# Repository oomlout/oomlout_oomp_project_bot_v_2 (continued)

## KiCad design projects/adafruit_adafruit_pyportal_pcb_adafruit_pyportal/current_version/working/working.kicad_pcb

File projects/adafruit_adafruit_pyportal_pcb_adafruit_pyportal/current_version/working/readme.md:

# adafruit_pyportal_pcb
 
## summary 
* id: adafruit_adafruit_pyportal_pcb_adafruit_pyportal
* user: adafruit
* name: adafruit_pyportal_pcb
* board: adafruit_pyportal
* repo: https://github.com/adafruit/Adafruit-PyPortal-PCB

* src_file_repo_sch: 
* src_file_repo_sch_link: https://github.com/adafruit/Adafruit-PyPortal-PCB/tree/master/
* full details link: https://github.com/oomlout/oomlout_oomp_project_bot_v_2/tree/main/projects/adafruit_adafruit_pyportal_pcb_adafruit_pyportal/current_version/working  

## schematic  
  
[schematic (pdf)](working_schematic.pdf) 

## pcb  

[board (pdf)](working.pdf)  

## working_bom
| Id | Designator | Footprint | Quantity | Designation | Supplier and ref |  | None | 
| --- | --- | --- | --- | --- | --- | --- | --- | 
| 1 | C17,C19,C1 | 0603-NO | 3 | 0.1uF |  |  | [''] | 
| 2 | R20,R19,R15,R18,R6,R9,R8 | 0603-NO | 7 | 10K |  |  | [''] | 
| 3 | U$2 | PQFN64-1 | 1 | ATSAMD51J20 |  |  | [''] | 
| 4 | D2,D1 | SOD-323 | 2 | 3.6V |  |  | [''] | 
| 5 | X3 | 2X05_1.27MM_SMT | 1 | 2x5 0.05 SWD" |  |  | [''] | 
| 6 | C14,C16,C11,C15,C12,C10 | 0603-NO | 6 | .1u |  |  | [''] | 
| 7 | CON1 | 53398-0271 | 1 | CON_MOLEX_2P |  |  | [''] | 
| 8 | LED1 | LED3535 | 1 | WS2812B3535 |  |  | [''] | 
| 9 | U$16,U$7,U$15,U$17 | MOUNTINGHOLE_3.0_PLATEDTHIN | 4 | MOUNTINGHOLE3.0THIN |  |  | [''] | 
| 10 | TP8,TP9,TP7 | TESTPOINT_ROUND_1.5MM | 3 |  |  |  | [''] | 
| 11 | U$23,U$11,U$9 | FIDUCIAL_1MM | 3 | FIDUCIAL_1MM |  |  | [''] | 
| 12 | C24,C3,C13,C22,C2,C20,C23,C5,C18,C8,C7,C21,C6 | 0805-NO | 13 | 10uF |  |  | [''] | 
| 13 | IC2 | SOT23-6 | 1 | PAM8301 |  |  | [''] | 
| 14 | R21,R22 | 0603-NO | 2 | 47K |  |  | [''] | 
| 15 | SJ4 | SOLDERJUMPER_CLOSEDWIRE | 1 |  |  |  | [''] | 
| 16 | X1 | MICROSD | 1 | microSD |  |  | [''] | 
| 17 | X4 | 4UCONN_20329_NARROW | 1 | microUSB |  |  | [''] | 
| 18 | R5,R12,R11,R10 | 0603-NO | 4 | 1K |  |  | [''] | 
| 19 | U4 | ALS-PT26-21C | 1 | ALS-PT21 |  |  | [''] | 
| 20 | RESET0 | EVQ-Q2_SMALLER | 1 | EVQQ 6mm |  |  | [''] | 
| 21 | R13 | RESPACK_4X0603 | 1 | 100 |  |  | [''] | 
| 22 | U1 | SOT23-5 | 1 | AP2112-3.3 |  |  | [''] | 
| 23 | Q1 | SOT23-BEC | 1 | MMBT2222 |  |  | [''] | 
| 24 | I2C0 | JSTPH4 | 1 | JST PH 4 |  |  | [''] | 
| 25 | SP1 | BUZZER_SMT_7.5MM | 1 | 7.5mm SPK |  |  | [''] | 
| 26 | PTC1 | 1206 | 1 | 500mA |  |  | [''] | 
| 27 | NEOPIX0,SENSE0 | JSTPH3 | 2 | JST PH 3 |  |  | [''] | 
| 28 | IC1 | SOT23-5L | 1 | 74AHC1G125 |  |  | [''] | 
| 29 | R4 | RESPACK_4X0603 | 1 | 10K |  |  | [''] | 
| 30 | C4 | 0805-NO | 1 | 0.1uF |  |  | [''] | 
| 31 | U$19 | PYPORTALPYNT_TOP | 1 |  |  |  | [''] | 
| 32 | U2 | SOIC8_208MIL | 1 | GD25Q64 |  |  | [''] | 
| 33 | IC3 | SOIC8_150MIL | 1 | ATECCX08 |  |  | [''] | 
| 34 | Q4 | SOT363 | 1 | BSS138 |  |  | [''] | 
| 35 | U$63 | PCBFEAT-REV-040 | 1 |  |  |  | [''] | 
| 36 | L0 | CHIPLED_0805_NOOUTLINE | 1 | RED |  |  | [''] | 
| 37 | U3 | ARDUINO-UCS&SOCS_NINA-W1X | 1 | NINA-W102 |  |  | [''] | 
| 38 | SJ1 | SOLDERJUMPER_2WAY_OPEN_NOPASTE | 1 |  |  |  | [''] | 
| 39 | C9 | 0603-NO | 1 | 1uF |  |  | [''] | 
| 40 | U$55 | TFT_2.4IN_240X320_50PIN | 1 | DISP_LCD_240X320_50PIN-2.4IN |  |  | [''] | 
| 41 | U$54 | PYPORTALPYNT_BOT | 1 |  |  |  | [''] | 

## bom_schematic
| Ref | Qnty | Value | Cmp name | Footprint | Description | Vendor | DNP | 
| --- | --- | --- | --- | --- | --- | --- | --- | 
| C1, C17, C19 | 3 | 0.1uF | CAP_CERAMIC0603_NO | working:0603-NO |  |  |  | 
| C2, C3, C5, C6, C7, C8, C13, C18, C20, C21, C22, C23, C24 | 13 | 10uF | CAP_CERAMIC0805-NOOUTLINE | working:0805-NO |  |  |  | 
| C4 | 1 | 0.1uF | CAP_CERAMIC0805-NOOUTLINE | working:0805-NO |  |  |  | 
| C9 | 1 | 1uF | CAP_CERAMIC0603_NO | working:0603-NO |  |  |  | 
| C10, C11, C12, C14, C15, C16 | 6 | .1u | CAP_CERAMIC0603_NO | working:0603-NO |  |  |  | 
| CON1 | 1 | CON_MOLEX_2P | CON_MOLEX_2P | working:53398-0271 |  |  |  | 
| D1, D2 | 2 | 3.6V | DIODE-ZENERSOD323 | working:SOD-323 |  |  |  | 
| I2C0 | 1 | STEMMA_I2C_RASMT | STEMMA_I2C_RASMT | working:JSTPH4 |  |  |  | 
| IC1 | 1 | 74AHC1G125 | 74AHC1G125 | working:SOT23-5L |  |  |  | 
| IC2 | 1 | PAM8301 | PAM8301 | working:SOT23-6 |  |  |  | 
| IC3 | 1 | ATECCX08 | ATECCX08 | working:SOIC8_150MIL |  |  |  | 
| L0 | 1 | RED | LED0805_NOOUTLINE | working:CHIPLED_0805_NOOUTLINE |  |  |  | 
| LED1 | 1 | WS2812B3535 | WS2812B3535 | working:LED3535 |  |  |  | 
| NEOPIX0 | 1 | JST PH 3 | CON_JST_PH_3PIN | working:JSTPH3 |  |  |  | 
| PTC1 | 1 | 500mA | PTC1206 | working:1206 |  |  |  | 
| Q1 | 1 | MMBT2222 | -NPN-SOT23-BEC | working:SOT23-BEC |  |  |  | 
| Q4 | 1 | BSS138 | MOSFET-N_DUAL | working:SOT363 |  |  |  | 
| R4 | 1 | 10K | RESISTOR_4PACK | working:RESPACK_4X0603 |  |  |  | 
| R5, R10, R11, R12 | 4 | 1K | RESISTOR_0603_NOOUT | working:0603-NO |  |  |  | 
| R6, R8, R9, R15, R18, R19, R20 | 7 | 10K | RESISTOR_0603_NOOUT | working:0603-NO |  |  |  | 
| R13 | 1 | 100 | RESISTOR_4PACK | working:RESPACK_4X0603 |  |  |  | 
| R21, R22 | 2 | 47K | RESISTOR_0603_NOOUT | working:0603-NO |  |  |  | 
| RESET0 | 1 | EVQQ 6mm | SWITCH_TACT_SMT_EVQQ2_SMALL | working:EVQ-Q2_SMALLER |  |  |  | 
| SENSE0 | 1 | JST PH 3 | CON_JST_PH_3PIN | working:JSTPH3 |  |  |  | 
| SJ1 | 1 | SOLDERJUMPER_2WAY | SOLDERJUMPER_2WAY | working:SOLDERJUMPER_2WAY_OPEN_NOPASTE |  |  |  | 
| SJ4 | 1 | SOLDERJUMPERCLOSED | SOLDERJUMPERCLOSED | working:SOLDERJUMPER_CLOSEDWIRE |  |  |  | 
| SP1 | 1 | SPEAKER_7.5MM | SPEAKER_7.5MM | working:BUZZER_SMT_7.5MM |  |  |  | 
| TP7, TP8, TP9 | 3 | TESTPOINTROUND1.5MM | TESTPOINTROUND1.5MM | working:TESTPOINT_ROUND_1.5MM |  |  |  | 
| U1 | 1 | AP2112-3.3 | VREG_SOT23-5 | working:SOT23-5 |  |  |  | 
| U2 | 1 | GD25Q64 | SPIFLASH_8PIN208MIL | working:SOIC8_208MIL |  |  |  | 
| U3 | 1 | NINA-W10XNINA-W10X | NINA-W10XNINA-W10X | working:ARDUINO-UCS&SOCS_NINA-W1X |  |  |  | 
| U4 | 1 | ALS-PT21 | PHOTOTRANSISTOR_PT26-21C | working:ALS-PT26-21C |  |  |  | 
| U$2 | 1 | ATSAMD51J | ATSAMD51J | working:PQFN64-1 |  |  |  | 
| U$7, U$15, U$16, U$17 | 4 | MOUNTINGHOLE3.0THIN | MOUNTINGHOLE3.0THIN | working:MOUNTINGHOLE_3.0_PLATEDTHIN |  |  |  | 
| U$9, U$11, U$23 | 3 | FIDUCIAL_1MM | FIDUCIAL_1MM | working:FIDUCIAL_1MM |  |  |  | 
| U$55 | 1 | DISP_LCD_240X320_50PIN-2.4IN | DISP_LCD_240X320_50PIN-2.4IN | working:TFT_2.4IN_240X320_50PIN |  |  |  | 
| X1 | 1 | microSD | MICROSD | working:MICROSD |  |  |  | 
| X3 | 1 | 2x5 0.05" SWD | JTAG-CORTEX | working:2X05_1.27MM_SMT |  |  |  | 
| X4 | 1 | microUSB | USB_MICRO_NARROW | working:4UCONN_20329_NARROW |  |  |  | 

## mounting_holes
| x | y | package | value | ref | size | 
| --- | --- | --- | --- | --- | --- | 
| 61.72 | 0.0 | MOUNTINGHOLE_3.0_PLATEDTHIN | MOUNTINGHOLE3.0THIN | U$7 | m3 | 
| 61.72 | 47.88 | MOUNTINGHOLE_3.0_PLATEDTHIN | MOUNTINGHOLE3.0THIN | U$15 | m3 | 
| 0.0 | 0.0 | MOUNTINGHOLE_3.0_PLATEDTHIN | MOUNTINGHOLE3.0THIN | U$16 | m3 | 
| 0.0 | 47.88 | MOUNTINGHOLE_3.0_PLATEDTHIN | MOUNTINGHOLE3.0THIN | U$17 | m3 |

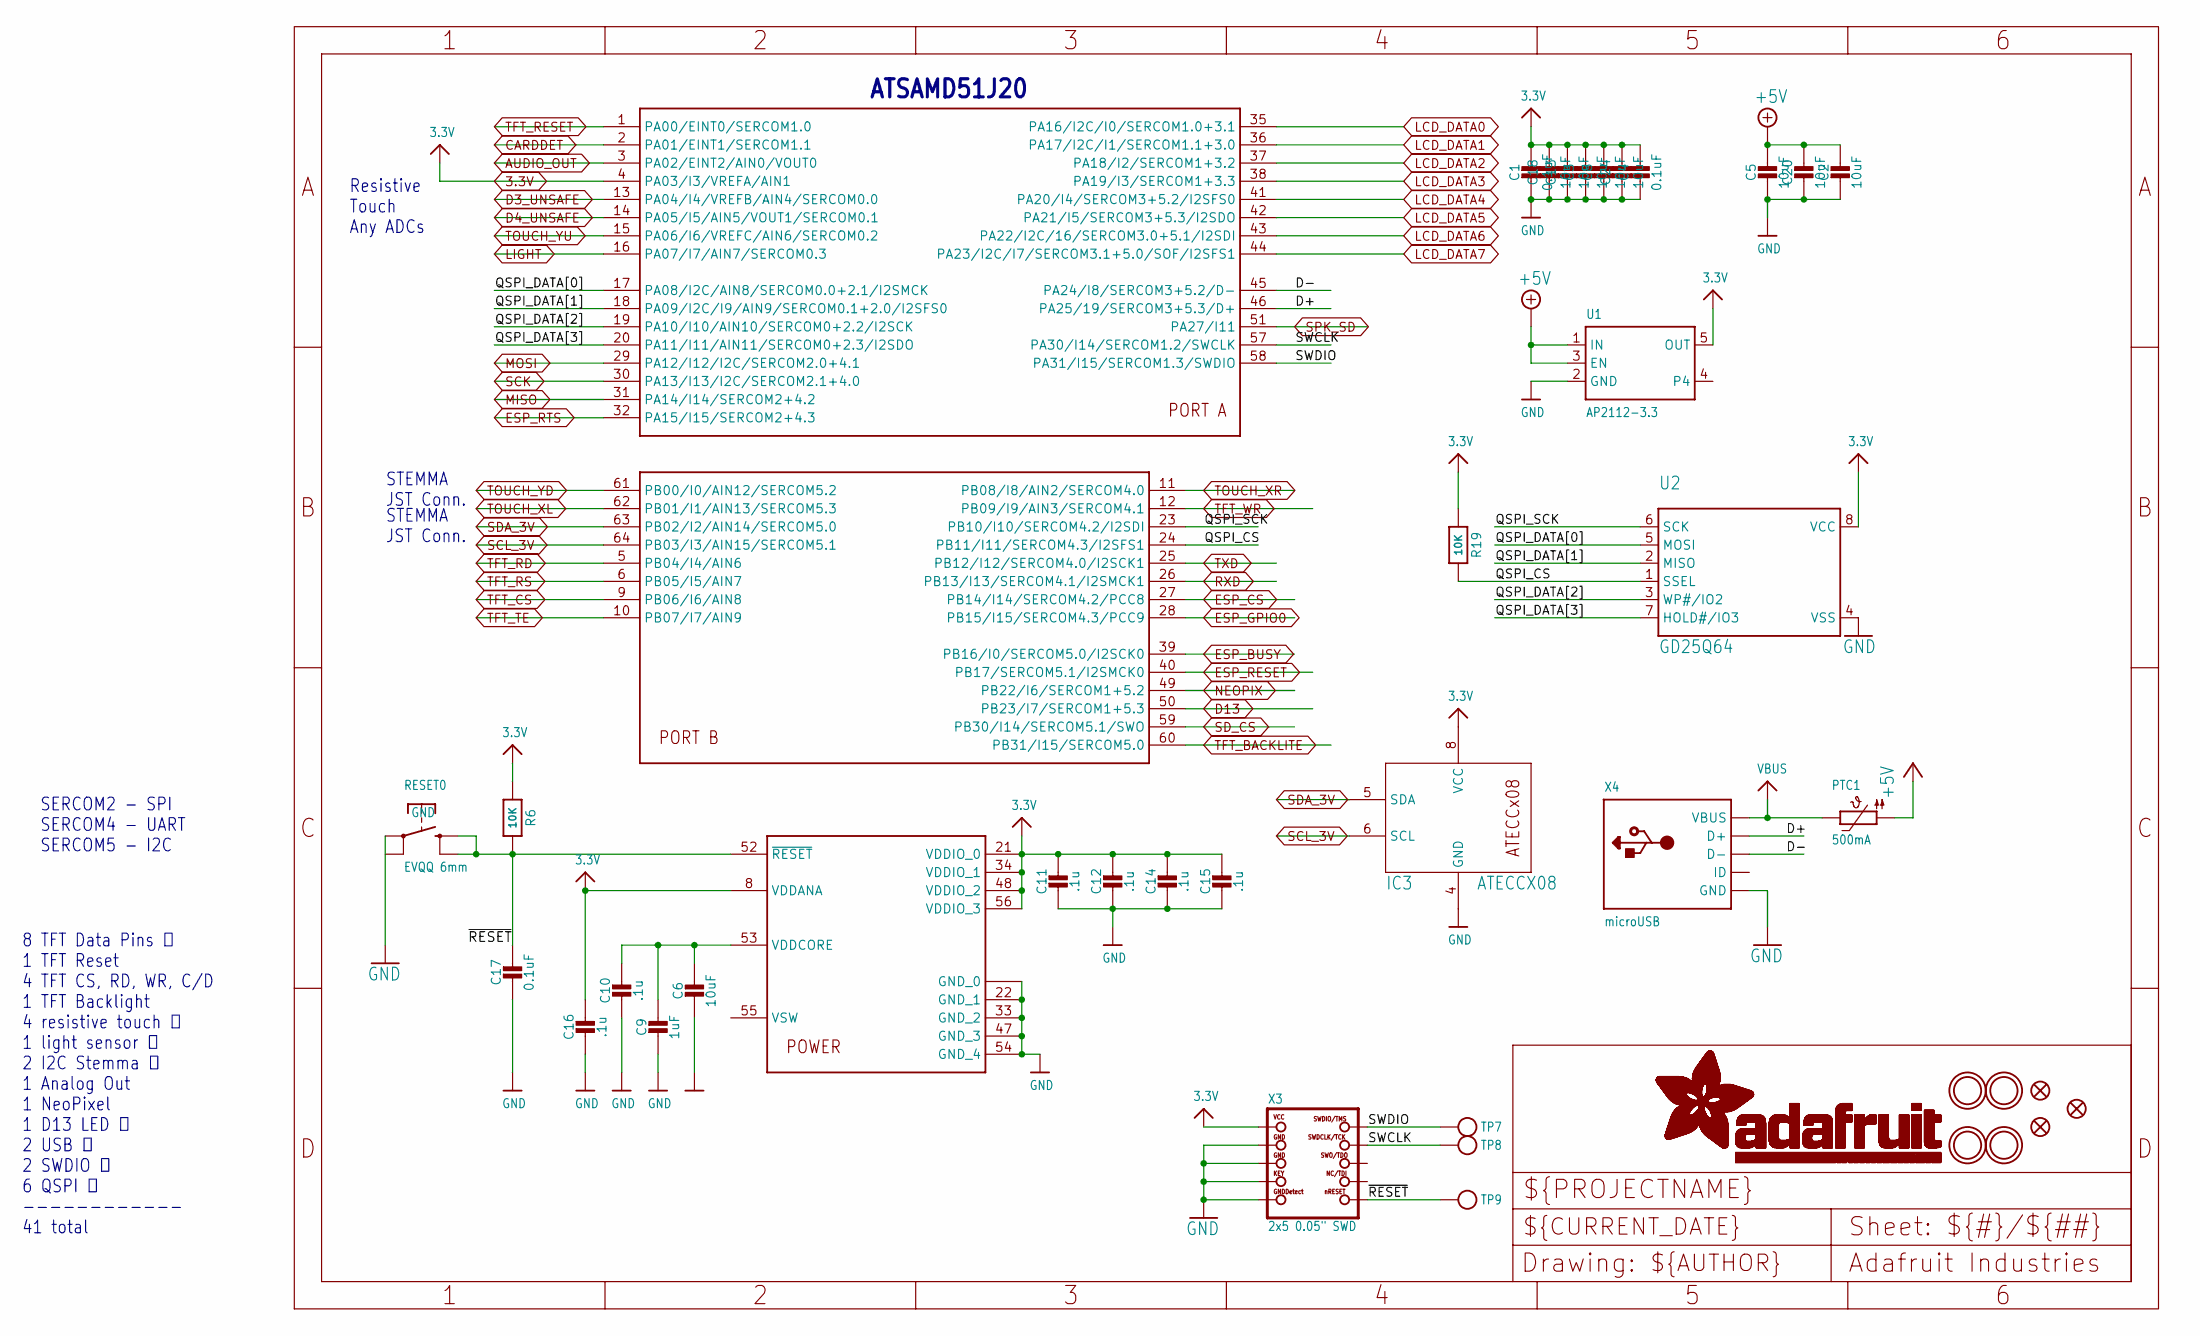
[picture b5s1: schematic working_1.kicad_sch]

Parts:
C1, C17: 0.1uF; 0603-NO
C2, C3, C5, C6, C8, C13, C18, C20, C24: 10uF; 0805-NO
C4: 0.1uF; 0805-NO
C9: 1uF; 0603-NO
C10, C11, C12, C14, C15, C16: .1u; 0603-NO
IC3: ATECCX08; SOIC8_150MIL
PTC1: 500mA; 1206
R6, R19: 10K; 0603-NO
RESET0: EVQQ 6mm; EVQ-Q2_SMALLER
TP7, TP8, TP9: TESTPOINTROUND1.5MM; TESTPOINT_ROUND_1.5MM
U1: AP2112-3.3; SOT23-5
U2: GD25Q64; SOIC8_208MIL
U$2: ATSAMD51J; PQFN64-1
U$7, U$15, U$16, U$17: MOUNTINGHOLE3.0THIN; MOUNTINGHOLE_3.0_PLATEDTHIN
U$9, U$11, U$23: FIDUCIAL_1MM
X3: 2x5 0.05" SWD; 2X05_1.27MM_SMT
X4: microUSB; 4UCONN_20329_NARROW

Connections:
3.3V: C1.1, C3.1, C4.1, C8.1, C11.2, C12.2, C13.1, C14.2, C15.2, C16.2, C18.1, C24.1, IC3.8 (VCC), R6.1, R19.1, U1.5 (OUT), U2.8 (VCC), U$2.4 (PA03/I3/VREFA/AIN1), U$2.8 (VDDANA), U$2.21 (VDDIO_0), U$2.34 (VDDIO_1), U$2.48 (VDDIO_2), U$2.56 (VDDIO_3), X3.1 (VCC); also elsewhere on the board
+5V: C2.1, C5.1, C20.1, PTC1.1, U1.1 (IN), U1.3 (EN); also elsewhere on the board
AUDIO_OUT: U$2.3 (PA02/EINT2/AIN0/VOUT0); also elsewhere on the board
CARDDET: U$2.2 (PA01/EINT1/SERCOM1.1); also elsewhere on the board
D3_UNSAFE: U$2.13 (PA04/I4/VREFB/AIN4/SERCOM0.0); also elsewhere on the board
D4_UNSAFE: U$2.14 (PA05/I5/AIN5/VOUT1/SERCOM0.1); also elsewhere on the board
D13: U$2.50 (PB23/I7/SERCOM1+5.3); also elsewhere on the board
D+: U$2.46 (PA25/19/SERCOM3+5.3/D+), X4.D+
D-: U$2.45 (PA24/I8/SERCOM3+5.2/D-), X4.D-
ESP_BUSY: U$2.39 (PB16/I0/SERCOM5.0/I2SCK0); also elsewhere on the board
ESP_CS: U$2.27 (PB14/I14/SERCOM4.2/PCC8); also elsewhere on the board
ESP_GPIO0: U$2.28 (PB15/I15/SERCOM4.3/PCC9); also elsewhere on the board
ESP_RESET: U$2.40 (PB17/SERCOM5.1/I2SMCK0); also elsewhere on the board
ESP_RTS: U$2.32 (PA15/I15/SERCOM2+4.3); also elsewhere on the board
GND: C1.2, C2.2, C3.2, C4.2, C5.2, C6.2, C8.2, C9.2, C10.1, C11.1, C12.1, C13.2, C14.1, C15.1, C16.1, C17.1, C18.2, C20.2, C24.2, IC3.4 (GND), RESET0.A, RESET0.A' (P1), U1.2 (GND), U2.4 (VSS), U$2.7 (GND_0), U$2.22 (GND_1), U$2.33 (GND_2), U$2.47 (GND_3), U$2.54 (GND_4), U$2.EXP (GND_0), X3.3 (GND@1), X3.5 (GND@2), X3.7 (KEY), X3.9 (GNDDETECT), X4.BASE@1 (GND), X4.BASE@2 (GND), X4.GND, X4.SPRT@1 (GND), X4.SPRT@2 (GND), X4.SPRT@3 (GND), X4.SPRT@4 (GND); also elsewhere on the board
LCD_DATA0: U$2.35 (PA16/I2C/I0/SERCOM1.0+3.1); also elsewhere on the board
LCD_DATA1: U$2.36 (PA17/I2C/I1/SERCOM1.1+3.0); also elsewhere on the board
LCD_DATA2: U$2.37 (PA18/I2/SERCOM1+3.2); also elsewhere on the board
LCD_DATA3: U$2.38 (PA19/I3/SERCOM1+3.3); also elsewhere on the board
LCD_DATA4: U$2.41 (PA20/I4/SERCOM3+5.2/I2SFS0); also elsewhere on the board
LCD_DATA5: U$2.42 (PA21/I5/SERCOM3+5.3/I2SDO); also elsewhere on the board
LCD_DATA6: U$2.43 (PA22/I2C/16/SERCOM3.0+5.1/I2SDI); also elsewhere on the board
LCD_DATA7: U$2.44 (PA23/I2C/I7/SERCOM3.1+5.0/SOF/I2SFS1); also elsewhere on the board
LIGHT: U$2.16 (PA07/I7/AIN7/SERCOM0.3); also elsewhere on the board
MISO: U$2.31 (PA14/I14/SERCOM2+4.2); also elsewhere on the board
MOSI: U$2.29 (PA12/I12/I2C/SERCOM2.0+4.1); also elsewhere on the board
NEOPIX: U$2.49 (PB22/I6/SERCOM1+5.2); also elsewhere on the board
QSPI_CS: R19.2, U2.1 (SSEL), U$2.24 (PB11/I11/SERCOM4.3/I2SFS1)
QSPI_DATA[0]: U2.5 (MOSI), U$2.17 (PA08/I2C/AIN8/SERCOM0.0+2.1/I2SMCK)
QSPI_DATA[1]: U2.2 (MISO), U$2.18 (PA09/I2C/I9/AIN9/SERCOM0.1+2.0/I2SFS0)
QSPI_DATA[2]: U2.3 (WP#/IO2), U$2.19 (PA10/I10/AIN10/SERCOM0+2.2/I2SCK)
QSPI_DATA[3]: U2.7 (HOLD#/IO3), U$2.20 (PA11/I11/AIN11/SERCOM0+2.3/I2SDO)
QSPI_SCK: U2.6 (SCK), U$2.23 (PB10/I10/SERCOM4.2/I2SDI)
RXD: U$2.26 (PB13/I13/SERCOM4.1/I2SMCK1); also elsewhere on the board
SCK: U$2.30 (PA13/I13/I2C/SERCOM2.1+4.0); also elsewhere on the board
SCL_3V: IC3.6 (SCL), U$2.64 (PB03/I3/AIN15/SERCOM5.1); also elsewhere on the board
SDA_3V: IC3.5 (SDA), U$2.63 (PB02/I2/AIN14/SERCOM5.0); also elsewhere on the board
SD_CS: U$2.59 (PB30/I14/SERCOM5.1/SWO); also elsewhere on the board
SPK_SD: U$2.51 (PA27/I11); also elsewhere on the board
SWCLK: TP8.P$1, U$2.57 (PA30/I14/SERCOM1.2/SWCLK), X3.4 (SWDCLK)
SWDIO: TP7.P$1, U$2.58 (PA31/I15/SERCOM1.3/SWDIO), X3.2 (SWDIO)
TFT_BACKLITE: U$2.60 (PB31/I15/SERCOM5.0); also elsewhere on the board
TFT_CS: U$2.9 (PB06/I6/AIN8); also elsewhere on the board
TFT_RD: U$2.5 (PB04/I4/AIN6); also elsewhere on the board
TFT_RESET: U$2.1 (PA00/EINT0/SERCOM1.0); also elsewhere on the board
TFT_RS: U$2.6 (PB05/I5/AIN7); also elsewhere on the board
TFT_TE: U$2.10 (PB07/I7/AIN9); also elsewhere on the board
TFT_WR: U$2.12 (PB09/I9/AIN3/SERCOM4.1); also elsewhere on the board
TOUCH_XL: U$2.62 (PB01/I1/AIN13/SERCOM5.3); also elsewhere on the board
TOUCH_XR: U$2.11 (PB08/I8/AIN2/SERCOM4.0); also elsewhere on the board
TOUCH_YD: U$2.61 (PB00/I0/AIN12/SERCOM5.2); also elsewhere on the board
TOUCH_YU: U$2.15 (PA06/I6/VREFC/AIN6/SERCOM0.2); also elsewhere on the board
TXD: U$2.25 (PB12/I12/SERCOM4.0/I2SCK1); also elsewhere on the board
VBUS: PTC1.2, X4.VBUS
VDDCORE: C6.1, C9.1, C10.2, U$2.53 (VDDCORE)
~RESET: C17.2, R6.2, RESET0.B (S), RESET0.B' (S1), TP9.P$1, U$2.52 (~RESET), X3.10 (NRESET)

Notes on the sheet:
Resistive Touch Any ADCs
ATSAMD51J20
STEMMA JST Conn.
SERCOM2 - SPI SERCOM4 - UART SERCOM5 - I2C
8 TFT Data Pins ✓ 1 TFT Reset 4 TFT CS, RD, WR, C/D 1 TFT Backlight 4 resistive touch ✓ 1 light sensor ✓ 2 I2C Stemma ✓ 1 Analog Out 1 NeoPixel 1 D13 LED ✓ 2 USB ✓ 2 SWDIO ✓ 6 QSPI ✓ ------------ 41 total

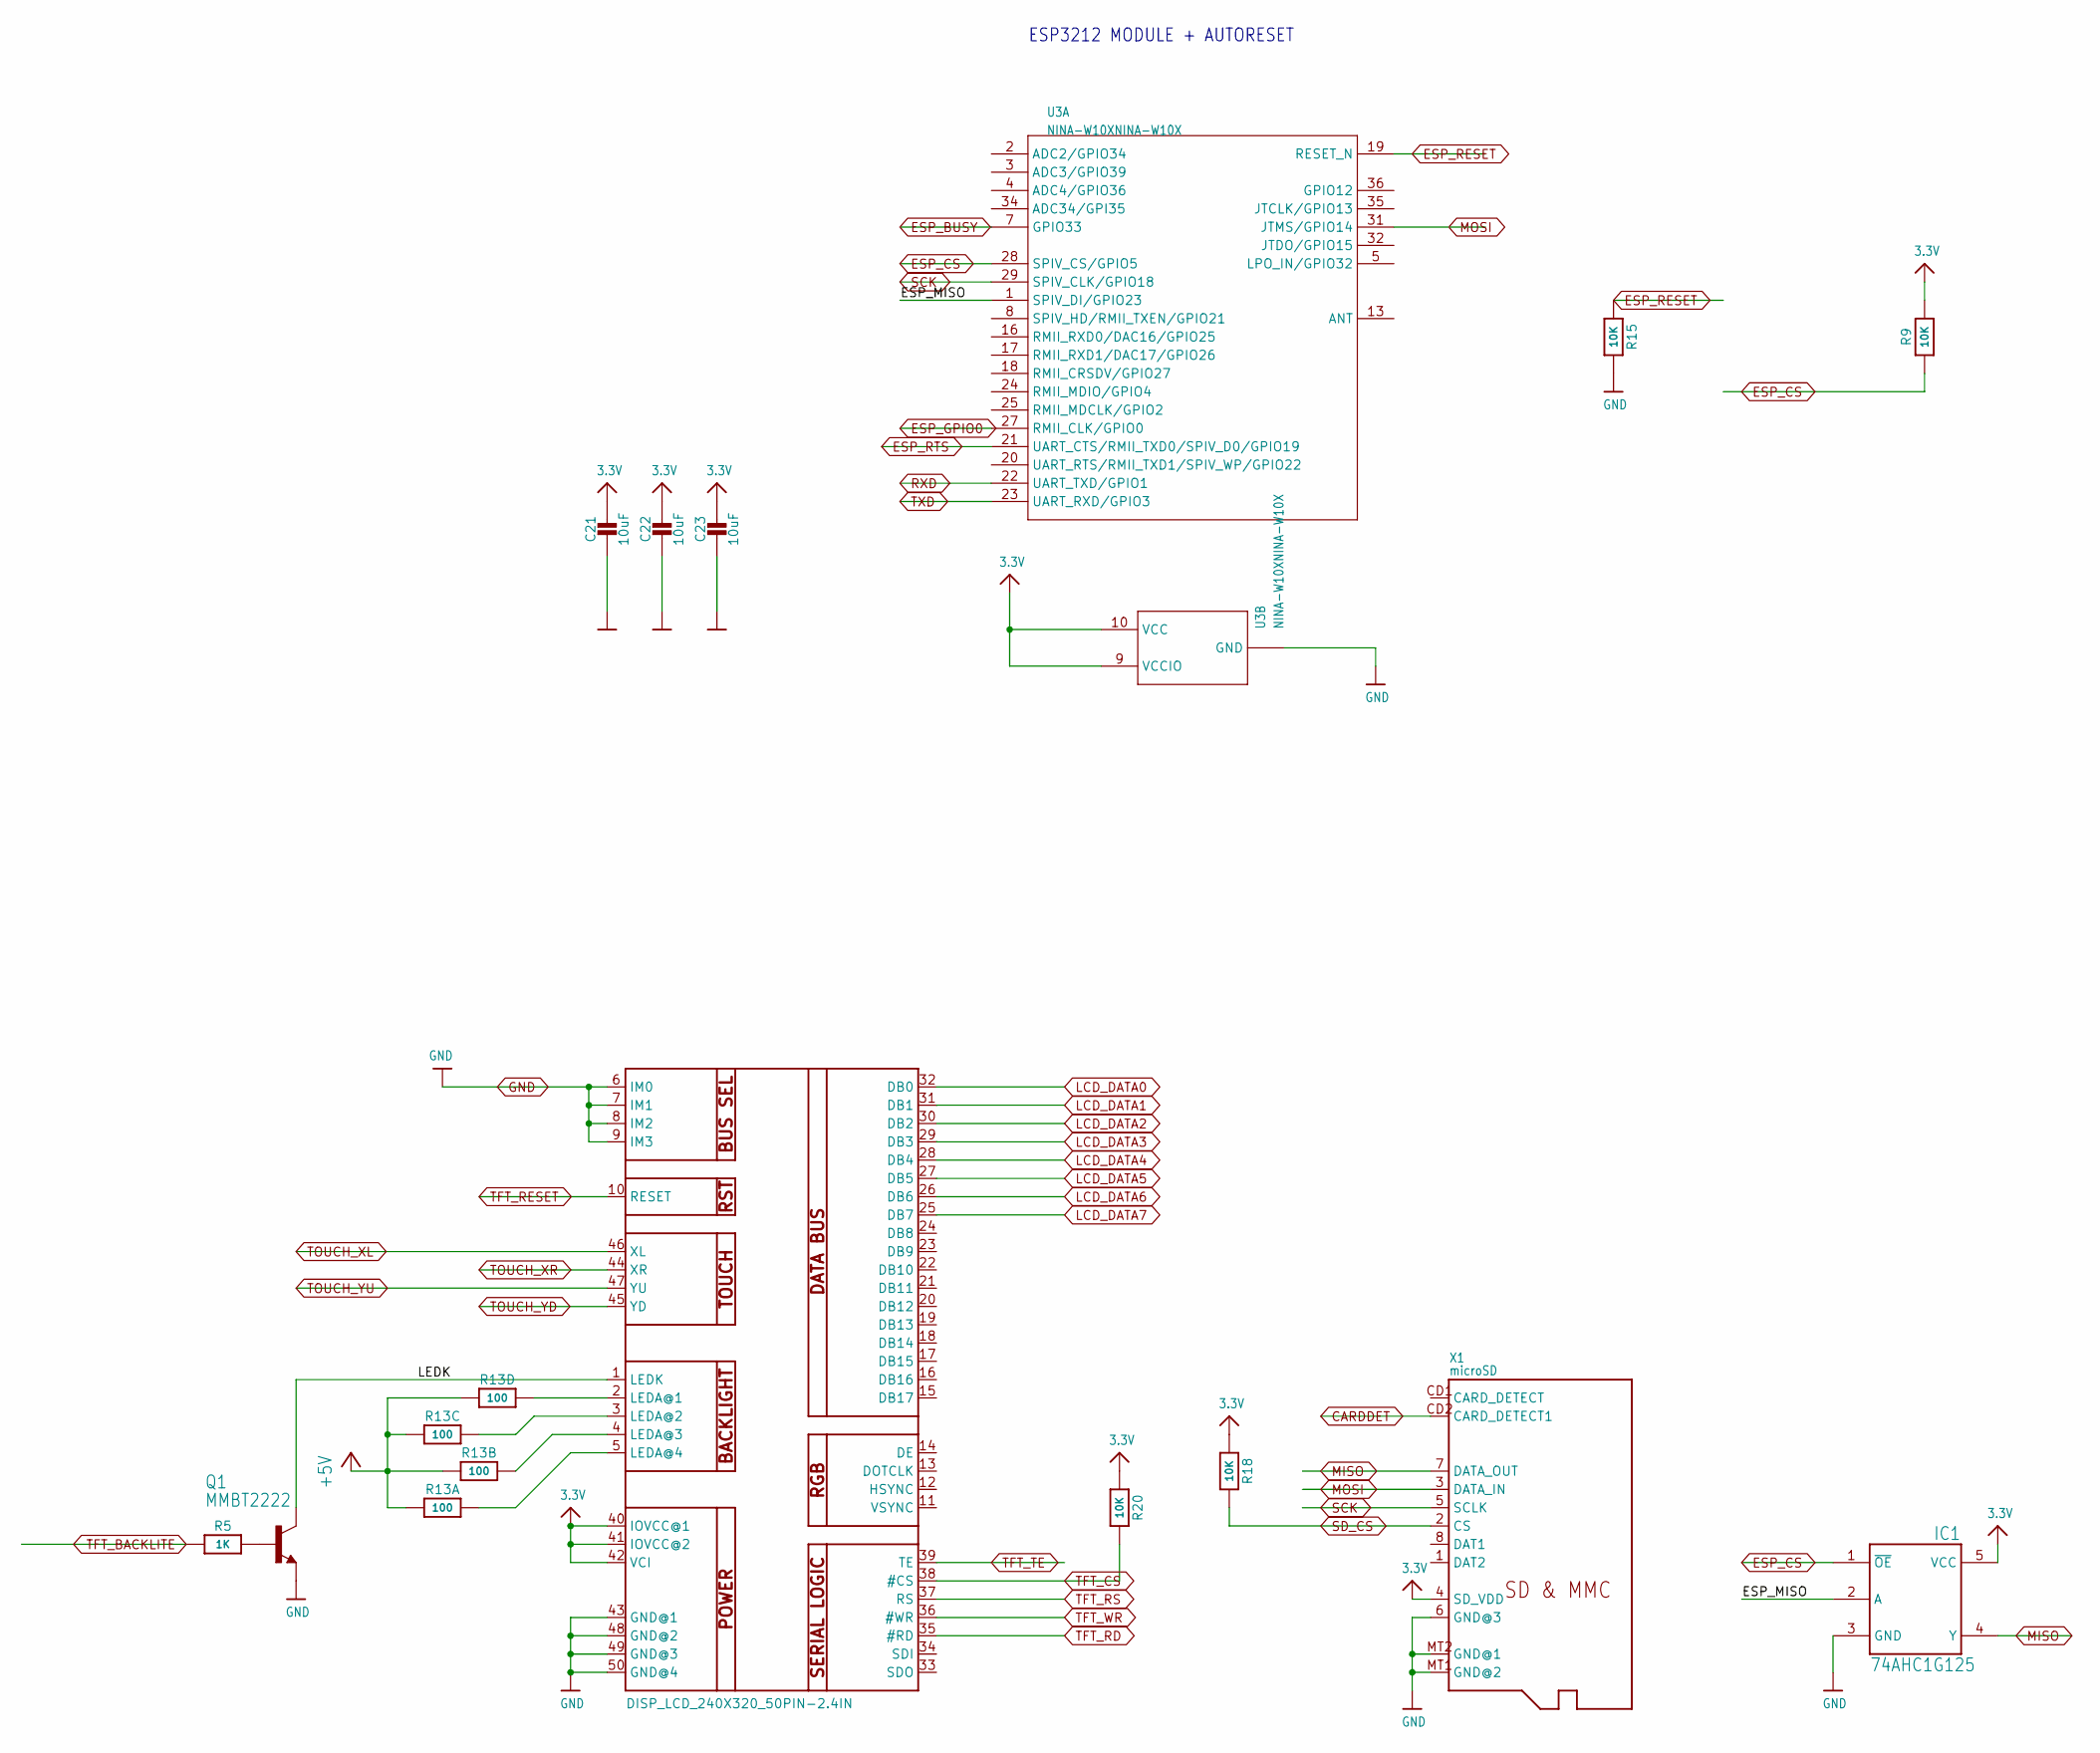
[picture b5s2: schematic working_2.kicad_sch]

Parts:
C21, C22, C23: 10uF; 0805-NO
IC1: 74AHC1G125; SOT23-5L
Q1: MMBT2222; SOT23-BEC
R5: 1K; 0603-NO
R9, R15, R18, R20: 10K; 0603-NO
R13: 100; RESPACK_4X0603
U3: NINA-W10XNINA-W10X; ARDUINO-UCS&SOCS_NINA-W1X
U$55: DISP_LCD_240X320_50PIN-2.4IN; TFT_2.4IN_240X320_50PIN
X1: microSD; MICROSD

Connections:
3.3V: C21.1, C22.1, C23.1, IC1.5 (VCC), R9.2, R18.1, R20.1, U3.9 (VCCIO), U3.10 (VCC), U$55.40 (IOVCC@1), U$55.41 (IOVCC@2), U$55.42 (VCI), X1.4 (SD_VDD); also elsewhere on the board
+5V: R13.1, R13.2 (1), R13.3 (1), R13.4 (1); also elsewhere on the board
CARDDET: X1.CD2 (CARD_DETECT1); also elsewhere on the board
ESP_BUSY: U3.7 (GPIO33); also elsewhere on the board
ESP_CS: IC1.1 (~OE), R9.1, U3.28 (SPIV_CS/GPIO5); also elsewhere on the board
ESP_GPIO0: U3.27 (RMII_CLK/GPIO0); also elsewhere on the board
ESP_MISO: IC1.2 (A), U3.1 (SPIV_DI/GPIO23)
ESP_RESET: R15.1, U3.19 (RESET_N); also elsewhere on the board
ESP_RTS: U3.21 (UART_CTS/RMII_TXD0/SPIV_D0/GPIO19); also elsewhere on the board
GND: C21.2, C22.2, C23.2, IC1.3 (GND), Q1.E, R15.2, U3.6 (GND), U3.12 (GND), U3.14 (GND), U3.26 (GND), U3.30 (GND), U3.GND@1 (GND), U3.GND@2 (GND), U3.GND@3 (GND), U3.GND@4 (GND), U3.GND@5 (GND), U3.GND@6 (GND), U3.GND@7 (GND), U3.GND@8 (GND), U3.GND@9 (GND), U3.GND@10 (GND), U3.GND@11 (GND), U3.GND@12 (GND), U$55.6 (IM0), U$55.7 (IM1), U$55.8 (IM2), U$55.9 (IM3), U$55.43 (GND@1), U$55.48 (GND@2), U$55.49 (GND@3), U$55.50 (GND@4), X1.6 (GND@3), X1.MT1 (GND@2), X1.MT2 (GND@1); also elsewhere on the board
LCD_DATA0: U$55.32 (DB0); also elsewhere on the board
LCD_DATA1: U$55.31 (DB1); also elsewhere on the board
LCD_DATA2: U$55.30 (DB2); also elsewhere on the board
LCD_DATA3: U$55.29 (DB3); also elsewhere on the board
LCD_DATA4: U$55.28 (DB4); also elsewhere on the board
LCD_DATA5: U$55.27 (DB5); also elsewhere on the board
LCD_DATA6: U$55.26 (DB6); also elsewhere on the board
LCD_DATA7: U$55.25 (DB7); also elsewhere on the board
LEDK: Q1.C, U$55.1 (LEDK)
MISO: IC1.4 (Y), X1.7 (DATA_OUT); also elsewhere on the board
MOSI: U3.31 (JTMS/GPIO14), X1.3 (DATA_IN); also elsewhere on the board
unnamed: R13.8 (2), U$55.5 (LEDA@4)
unnamed: R13.5 (2), U$55.2 (LEDA@1)
unnamed: R13.6 (2), U$55.3 (LEDA@2)
unnamed: R13.7 (2), U$55.4 (LEDA@3)
unnamed: Q1.B, R5.2
RXD: U3.22 (UART_TXD/GPIO1); also elsewhere on the board
SCK: U3.29 (SPIV_CLK/GPIO18), X1.5 (SCLK); also elsewhere on the board
SD_CS: R18.2, X1.2 (CS); also elsewhere on the board
TFT_BACKLITE: R5.1; also elsewhere on the board
TFT_CS: R20.2, U$55.38 (#CS); also elsewhere on the board
TFT_RD: U$55.35 (#RD); also elsewhere on the board
TFT_RESET: U$55.10 (RESET); also elsewhere on the board
TFT_RS: U$55.37 (RS); also elsewhere on the board
TFT_TE: U$55.39 (TE); also elsewhere on the board
TFT_WR: U$55.36 (#WR); also elsewhere on the board
TOUCH_XL: U$55.46 (XL); also elsewhere on the board
TOUCH_XR: U$55.44 (XR); also elsewhere on the board
TOUCH_YD: U$55.45 (YD); also elsewhere on the board
TOUCH_YU: U$55.47 (YU); also elsewhere on the board
TXD: U3.23 (UART_RXD/GPIO3); also elsewhere on the board

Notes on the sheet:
ESP3212 MODULE + AUTORESET

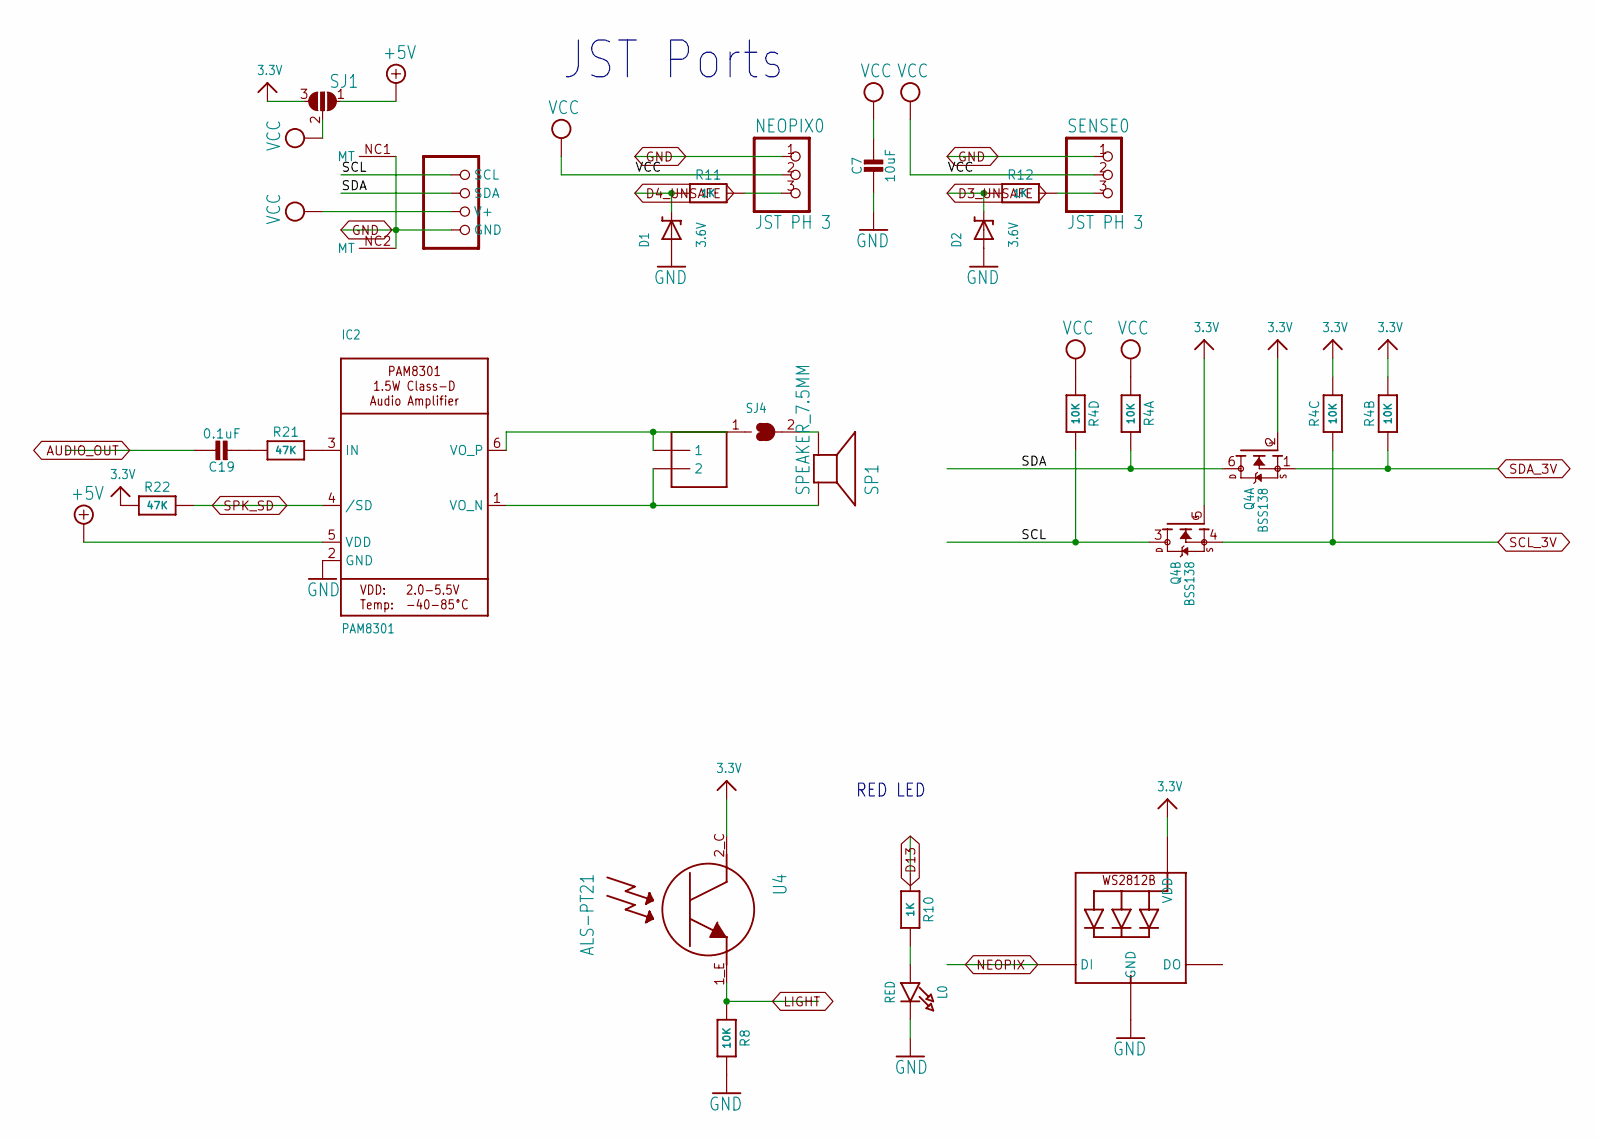
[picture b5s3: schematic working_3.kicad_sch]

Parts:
C7: 10uF; 0805-NO
C19: 0.1uF; 0603-NO
CON1: CON_MOLEX_2P; 53398-0271
D1, D2: 3.6V; SOD-323
I2C0: STEMMA_I2C_RASMT; JSTPH4
IC2: PAM8301; SOT23-6
L0: RED; CHIPLED_0805_NOOUTLINE
LED1: WS2812B3535; LED3535
NEOPIX0: JST PH 3; JSTPH3
Q4: BSS138; SOT363
R4: 10K; RESPACK_4X0603
R8: 10K; 0603-NO
R10, R11, R12: 1K; 0603-NO
R21, R22: 47K; 0603-NO
SENSE0: JST PH 3; JSTPH3
SJ1: SOLDERJUMPER_2WAY; SOLDERJUMPER_2WAY_OPEN_NOPASTE
SJ4: SOLDERJUMPERCLOSED; SOLDERJUMPER_CLOSEDWIRE
SP1: SPEAKER_7.5MM; BUZZER_SMT_7.5MM
U4: ALS-PT21; ALS-PT26-21C

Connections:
3.3V: LED1.2 (VDD), Q4.2 (G), Q4.5 (G), R4.2 (1), R4.3 (1), R22.1, SJ1.3, U4.2_C (C); also elsewhere on the board
+5V: IC2.5 (VDD), SJ1.1; also elsewhere on the board
AUDIO_OUT: C19.1; also elsewhere on the board
D3: R12.1, SENSE0.3
D3_UNSAFE: D2.C, R12.2; also elsewhere on the board
D4: NEOPIX0.3, R11.1
D4_UNSAFE: D1.C, R11.2; also elsewhere on the board
D13: R10.1; also elsewhere on the board
GND: C7.2, D1.A, D2.A, I2C0.1 (GND), I2C0.NC1 (MT), I2C0.NC2 (MT), IC2.2 (GND), L0.C, LED1.4 (GND), NEOPIX0.1, R8.1, SENSE0.1; also elsewhere on the board
LIGHT: R8.2, U4.1_E (E); also elsewhere on the board
unnamed: L0.A, R10.2
unnamed: C19.2, R21.1
unnamed: IC2.3 (IN), R21.2
unnamed: SJ4.2, SP1.-
NEOPIX: LED1.1 (DI); also elsewhere on the board
SCL: I2C0.4 (SCL), Q4.3 (D), R4.5 (2)
SCL_3V: Q4.4 (S), R4.6 (2); also elsewhere on the board
SDA: I2C0.3 (SDA), Q4.6 (D), R4.8 (2)
SDA_3V: Q4.1 (S), R4.7 (2); also elsewhere on the board
SPKR+: CON1.2, IC2.1 (VO_N), SP1.+
SPK_SD: IC2.4 (/SD), R22.2; also elsewhere on the board
SPRK-: CON1.1, IC2.6 (VO_P), SJ4.1
VCC: C7.1, I2C0.2 (V+), NEOPIX0.2, R4.1, R4.4 (1), SENSE0.2, SJ1.2

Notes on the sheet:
JST Ports
RED LED

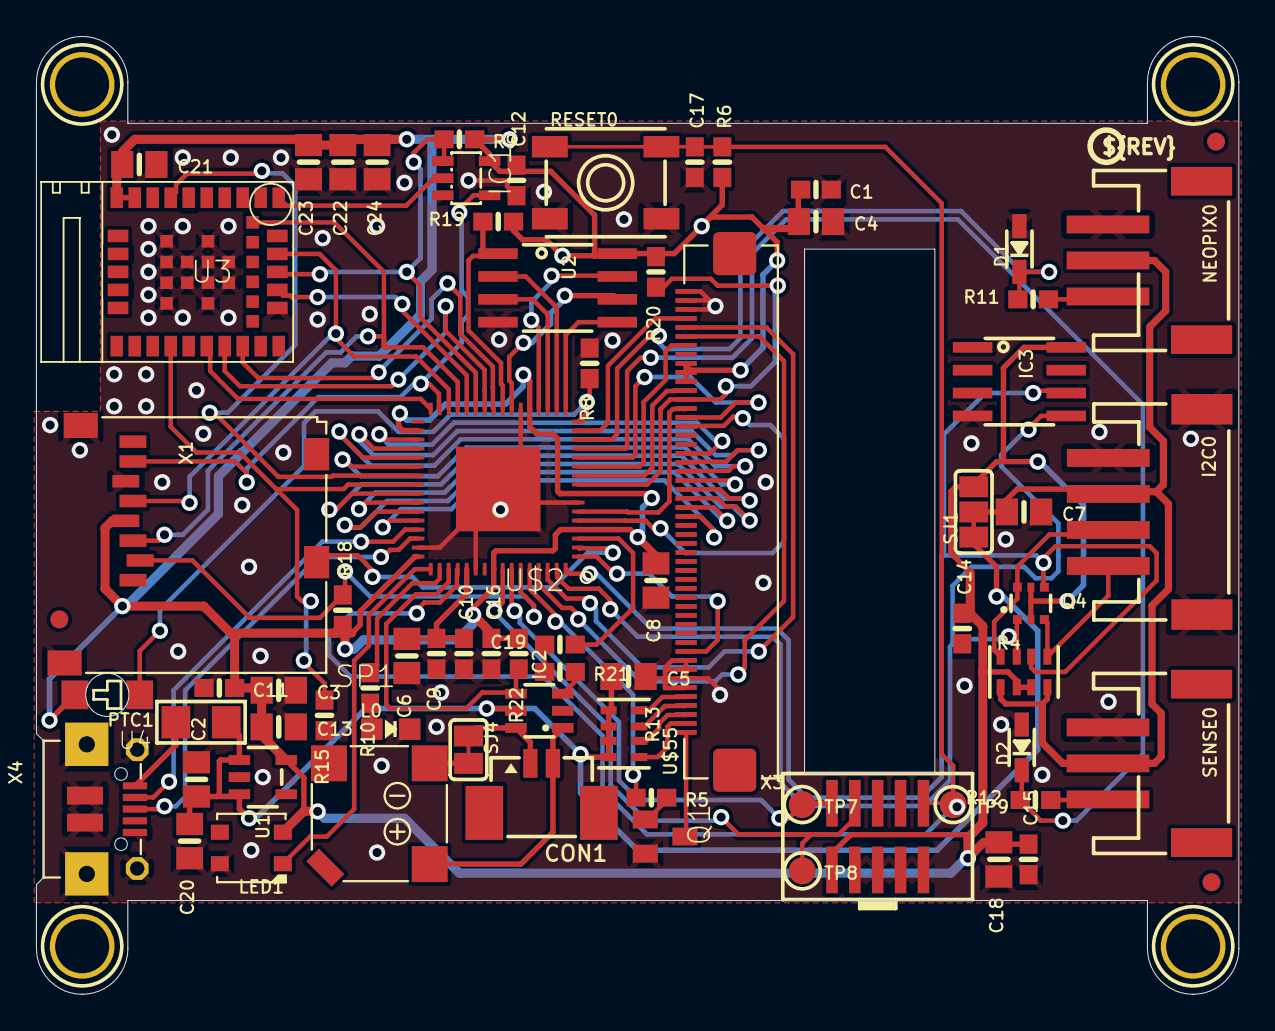
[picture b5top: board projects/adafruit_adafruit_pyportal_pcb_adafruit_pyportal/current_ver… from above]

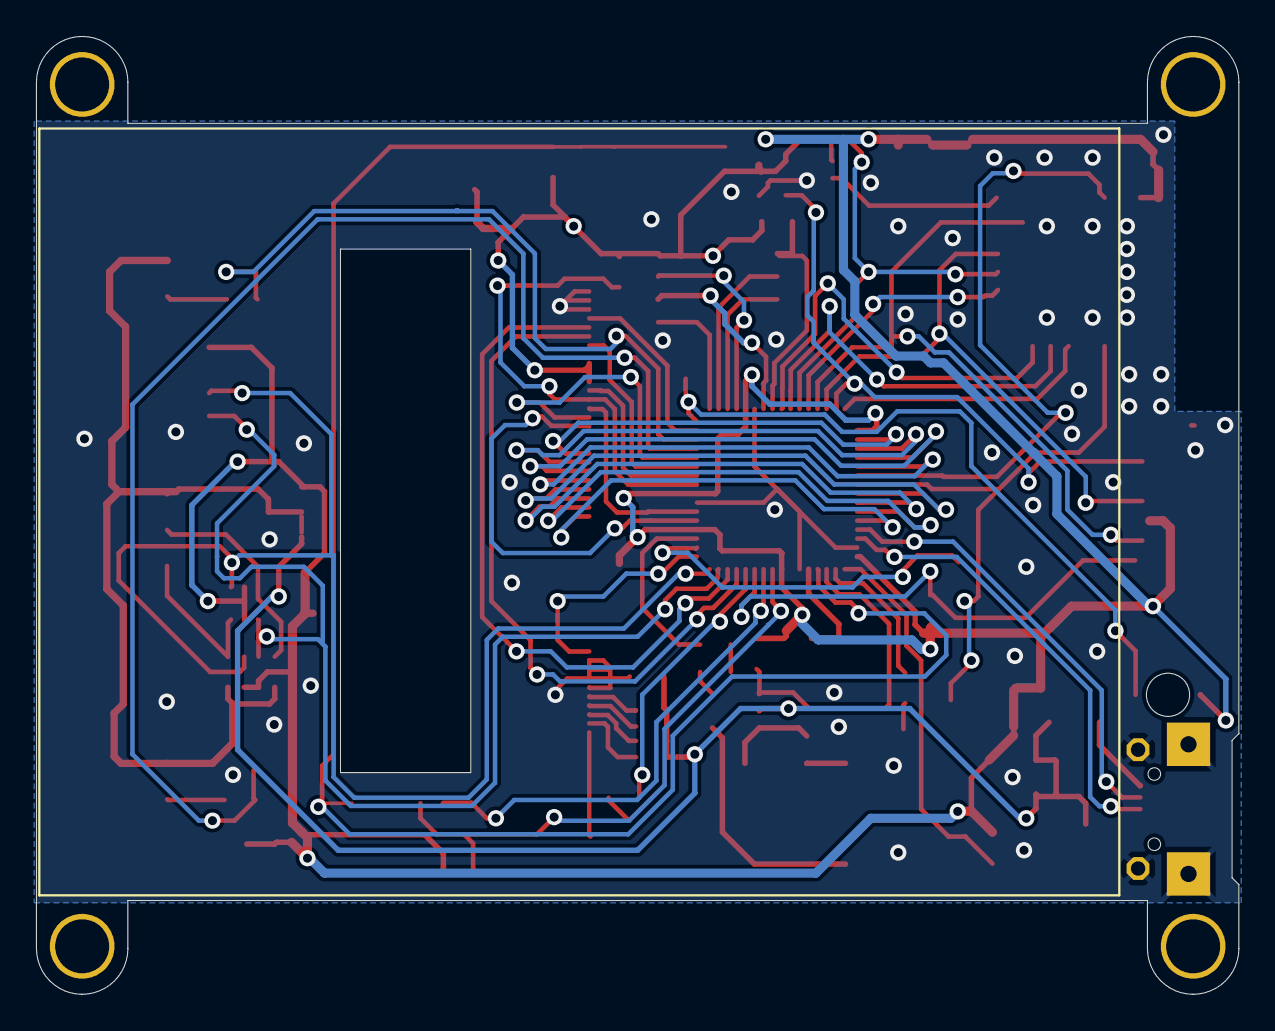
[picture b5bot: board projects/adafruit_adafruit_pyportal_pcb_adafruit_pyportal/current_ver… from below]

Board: 16 copper layers, 66.8 x 53.2 mm, 79 parts (2 on the bottom side), 74 nets.

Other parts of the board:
U$19: PYPORTALPYNT_TOP
U$54: PYPORTALPYNT_BOT
U$63: PCBFEAT-REV-040
